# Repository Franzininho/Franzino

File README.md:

# Franzino (ENG)

Franzino is a low cost Arduino standalone board. As its name suggests, is a simple board that has just the basic components so you can use the ATmega328P microcontroller, both for study and for applications in projects.

Unlike standalones available in the market, the Franzino board has pinout Arduino Rev 3 and connector for easy connection of the serial interface. The ease of access to the pins of the serial interface, enables you to connect communication modules according to the needs of the project. You will be able to easily connect serial level converters such as USB, RS232, RS485 and even a Bluetooth module, without the need to use shields.

Franzino uses Arduino UNO bootloader to facilitating the upload process of your scketch. You can easily upload your sketch to Franzino board using a USB to Serial converter, following the same steps that are already used to your Arduino UNO board.

# Characteristics:

- Arduino UNO R3 pinout;
- ATmega328P Microcontroller;
- Power: 7.5 V to 20 V DC;
- Protection against reverse polarity of the supply;
- Connector for serial interface connection;
- Power on LED;
- LED connected to pin 13 for general porpouse;

# Franzino (PT)

A placa Franzino é um Arduino standalone de baixo custo. Como seu próprio nome sugere, é uma placa enxuta que possui os componentes básicos para que você possa usar o microcontrolador ATmega328, tanto para estudo quanto para a aplicações em projetos.

Diferente dos standalones disponíveis no mercado, a placa Franzino possui pinagem Arduino UNO Rev 3 e conector para fácil ligação da interface serial. A facilidade de acesso aos pinos da interface serial, possibilita que você ligue módulos de comunicação conforme a necessidade do projeto. Você conseguirá facilmente ligar conversores de níveis seriais como: USB, RS232, RS485 e até mesmo um módulo Bluetooth, sem a necessidade do uso de shields.

A Franzino usa o bootloader do Arduino UNO facilitando o processo de upload do seu scketch. Você poderá facilmente fazer o upload do seu sketch para placa usando um conversor USB/Serial, seguindo os mesmos passos que já está acostumado a fazer com a placa Arduino UNO.

## Características:

- Pinagem Padrão UNO R3
- Microcontrolador ATmega328P;
- Alimentação: 7,5 V a 20 V DC;
- Proteção contra inversão de polaridade da fonte;
- Conector para ligação de interface serial;
- LED para indicação de alimentação;
- LED conectado ao pino 13 para uso geral

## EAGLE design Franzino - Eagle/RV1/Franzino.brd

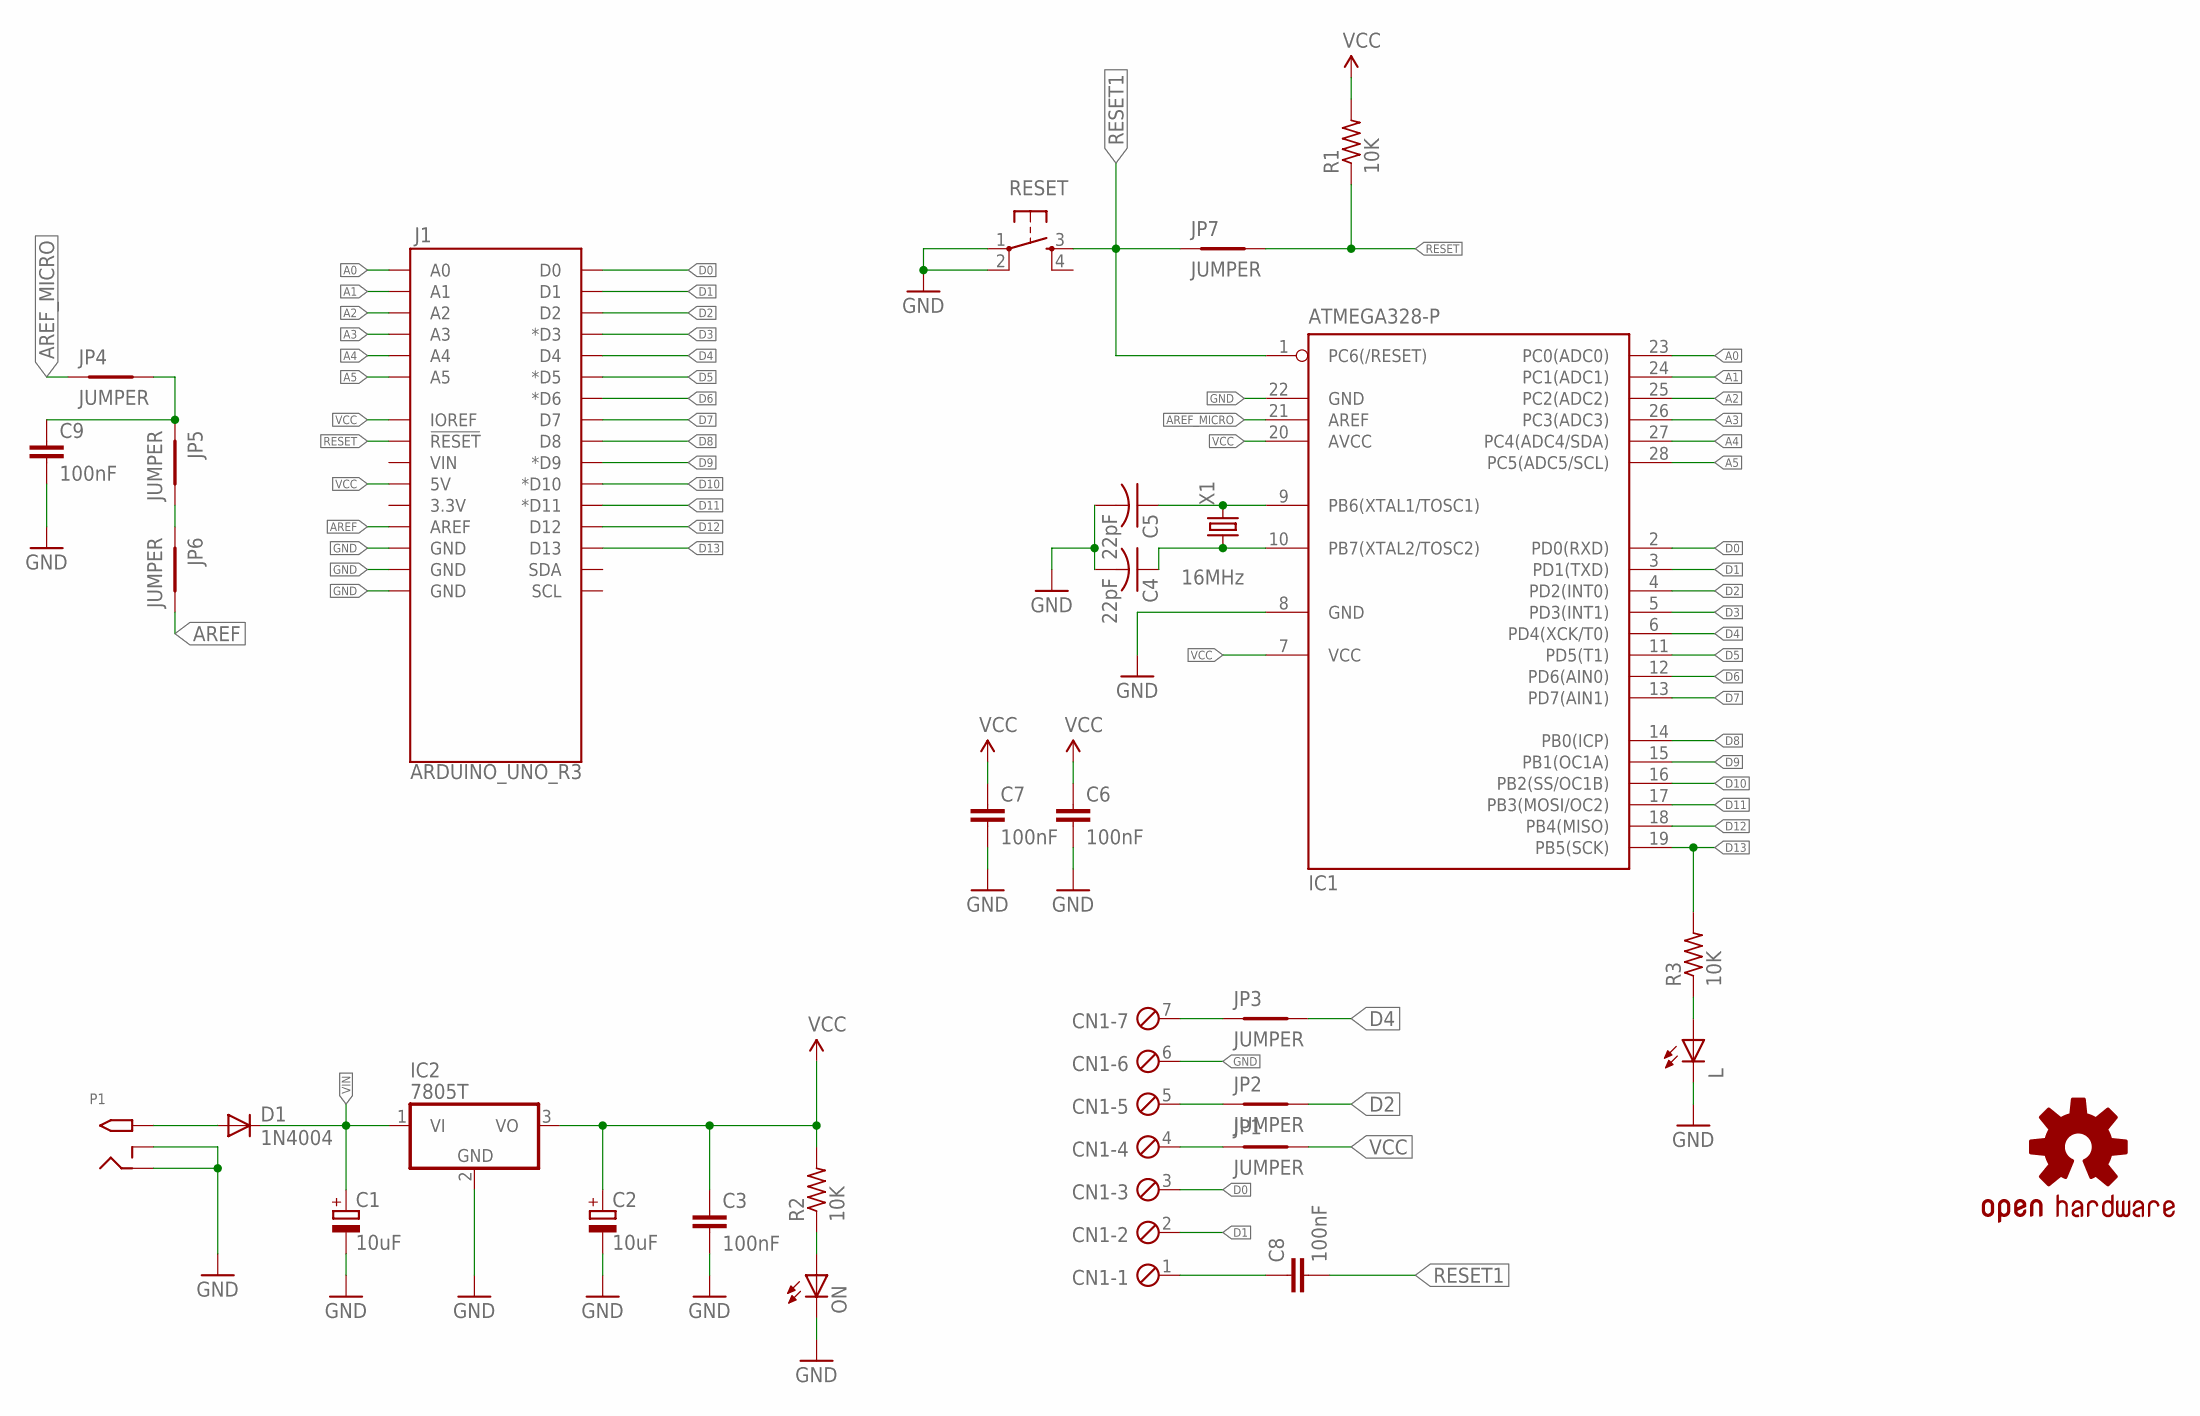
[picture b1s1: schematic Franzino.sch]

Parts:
C1, C2: 10uF; E2,5-6
C3, C6, C7, C8, C9: 100nF; C025-025X050
C4, C5: 22pF; C025-024X044
CN1: BARRA de PINOS 6 VIAS; 7POL254
D1: 1N4004; DO41-10
IC1: ATMEGA328-P; DIL28-3
IC2: 7805T; TO220H
J1: ARDUINO_UNO_R3; ARDUINO_UNO_R3_PINS
JP1, JP2, JP3, JP4, JP5, JP6, JP7: JUMPER; JUMP10
L: LED 3mm Amarelo; LED3MM
LOGO2: OSHW-LOGOL; OSHW-LOGO-L
ON: LED 3 mm VERDE; LED3MM
P1: 2.1MMJACKTHM; PJ-102A
R1, R2, R3: 10K; 0207/10
RESET: CHAVE TACTIL 6 mm; TACTILE-PTH
X1: 16MHz; HC49/S

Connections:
A0: IC1.23 (PC0(ADC0)), J1.A0
A1: IC1.24 (PC1(ADC1)), J1.A1
A2: IC1.25 (PC2(ADC2)), J1.A2
A3: IC1.26 (PC3(ADC3)), J1.A3
A4: IC1.27 (PC4(ADC4/SDA)), J1.A4
A5: IC1.28 (PC5(ADC5/SCL)), J1.A5
AREF: J1.AREF, JP6.2
AREF_MICRO: IC1.21 (AREF), JP4.1
D0: CN1.3, IC1.2 (PD0(RXD)), J1.D0
D1: CN1.2, IC1.3 (PD1(TXD)), J1.D1
D2: IC1.4 (PD2(INT0)), J1.D2, JP2.2
D3: IC1.5 (PD3(INT1)), J1.D3 (*D3)
D4: IC1.6 (PD4(XCK/T0)), J1.D4, JP3.2
D5: IC1.11 (PD5(T1)), J1.D5 (*D5)
D6: IC1.12 (PD6(AIN0)), J1.D6 (*D6)
D7: IC1.13 (PD7(AIN1)), J1.D7
D8: IC1.14 (PB0(ICP)), J1.D8
D9: IC1.15 (PB1(OC1A)), J1.D9 (*D9)
D10: IC1.16 (PB2(SS/OC1B)), J1.D10 (*D10)
D11: IC1.17 (PB3(MOSI/OC2)), J1.D11 (*D11)
D12: IC1.18 (PB4(MISO)), J1.D12
D13: IC1.19 (PB5(SCK)), J1.D13, R3.2
GND: C1.-, C2.-, C3.2, C4.2, C5.2, C6.2, C7.2, C9.2, CN1.6, IC1.8 (GND), IC1.22 (GND), IC2.2 (GND), J1.GND@1 (GND), J1.GND@2 (GND), J1.GND@3 (GND), L.K (C), ON.K (C), P1.RING, P1.RING_SW, RESET.1, RESET.2
unnamed: D1.A, P1.TIP
unnamed: L.A, R3.1
unnamed: C8.1, CN1.1
unnamed: CN1.4, JP1.1
unnamed: CN1.5, JP2.1
unnamed: ON.A, R2.1
unnamed: CN1.7, JP3.1
unnamed: C5.1, IC1.9 (PB6(XTAL1/TOSC1)), X1.2
unnamed: C4.1, IC1.10 (PB7(XTAL2/TOSC2)), X1.1
unnamed: C9.1, JP4.2, JP5.1
unnamed: JP5.2, JP6.1
RESET: J1.RESET@1 (!RESET!), JP7.2, R1.1
RESET1: C8.2, IC1.1 (PC6(/RESET)), JP7.1, RESET.3
VCC: C2.+, C3.1, C6.1, C7.1, IC1.7 (VCC), IC1.20 (AVCC), IC2.3 (VO), J1.5V, J1.IOREF, JP1.2, R1.2, R2.2
VIN: C1.+, D1.C, IC2.1 (VI)

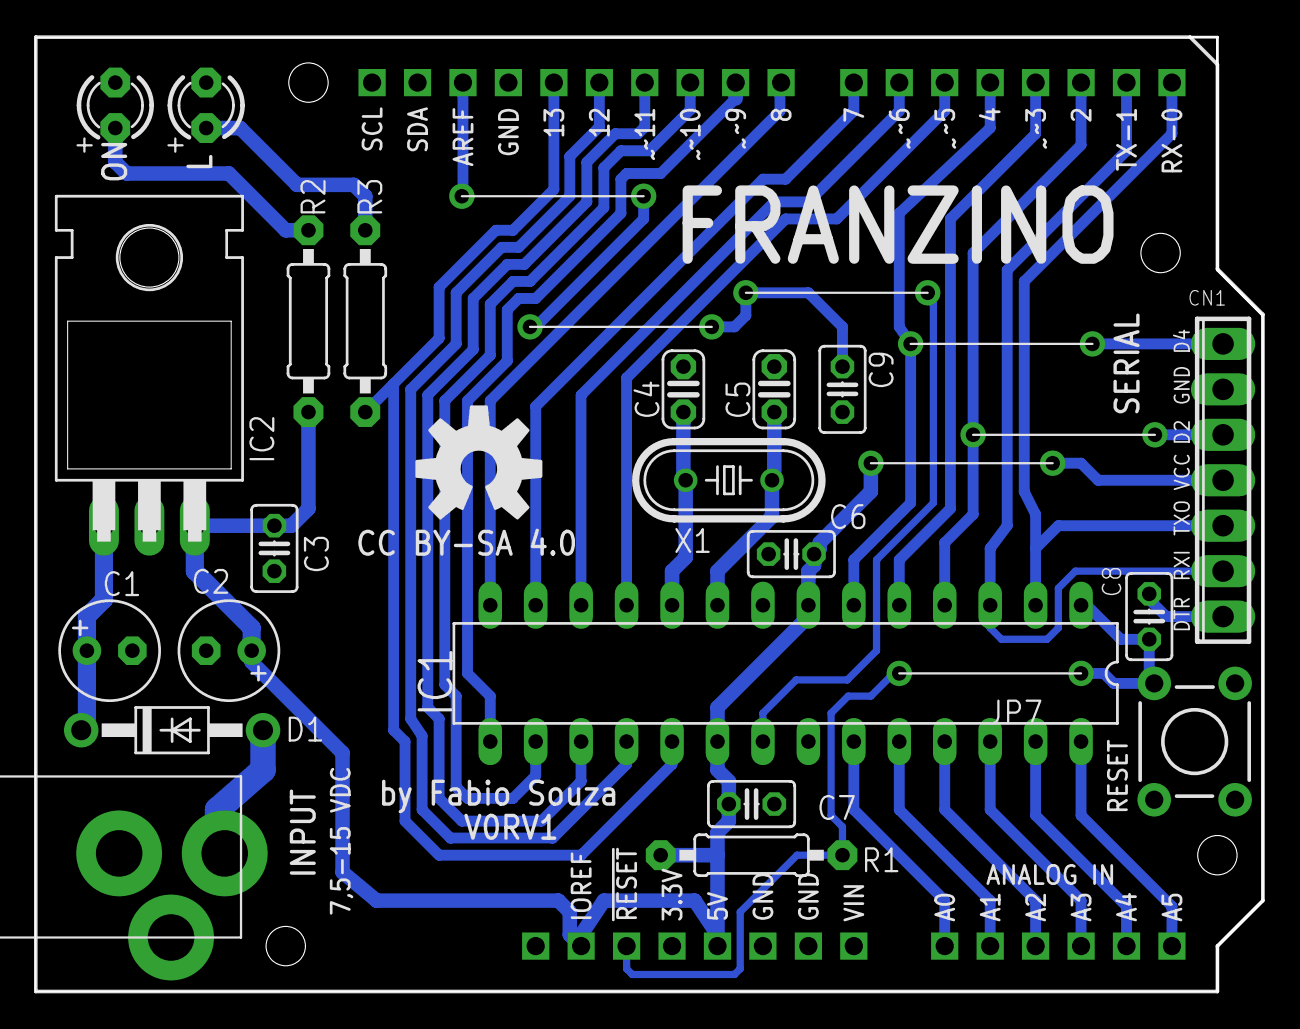
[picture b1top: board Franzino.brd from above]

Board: 2 copper layers, 68.5 x 53.3 mm, 30 parts (0 on the bottom side), 38 nets.

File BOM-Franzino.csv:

Placa,,Franzino,
,,,
Referência,Componente,quantidade,Valor
C1,10uF X 50V,1,
C2,10uF X 50V,1,
C3,100nF SMD 0805,1,
C4,22pF,1,
C5,22pF,1,
C6,100nF SMD 0805,1,
C7,100nF SMD 0806,1,
C8,100nF SMD 0807,1,
C9,100nF SMD 0808,1,
CN1,Barra de pinos 7 vias 90°,1,
D1,1n4007,1,
IC1,Soquete 28 pinos,1,
IC2,Regulador 7805,1,
J1,mini header simples 40 pinos,1,
JP1,JUMPER FIO 10 mm,1,
JP2,JUMPER FIO 10 mm,1,
JP3,JUMPER FIO 10 mm,1,
JP4,JUMPER FIO 10 mm,1,
JP5,JUMPER FIO 10 mm,1,
JP6,JUMPER FIO 10 mm,1,
L,LED 3 mm VERDE,1,
ON,LED 3 mm Amarelo,1,
P1,"JACK 2,1 mm ",1,
R1,Resistor 10 K 5%,1,
R2,Resistor 1 K 5%,1,
R3,Resistor 1 K 5%,1,
RESET,Chave Tactil 7 mm,1,
X1,Cristal 16 MHz,1,
PCB,Placa de circuito impresso Franzino,1,

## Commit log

2016-10-26 Franzino
    V0 RV1
2016-10-26 manual
    manual simplificado
2016-10-26 license
    CC 4.0
2017-03-27 license
2017-04-26 update - Pordução processo termico
2017-11-20 RV1
    Trocado capacitores de SMD por PTH
    Melhora no Silk
2018-02-20 gerber
2018-10-01 atualização RV1
2018-10-01 manual
2018-10-01 imagens
2018-10-01 imagem6
2018-10-01 informações em PT
2020-07-12 ajuste ortográfico
2021-07-21 Lista de componentes

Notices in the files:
Franzino - Eagle/RV1/Franzino.brd:
CC BY-SA 4.0
parts and their libraries:
SparkFun-Retired: Licensing:Creative Commons ShareAlike 4.0 International - https://creativecommons.org/licenses/by-sa/4.0
